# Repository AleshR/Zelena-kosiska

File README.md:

Zelena-kosiska
Pilot project of powerline communication modem

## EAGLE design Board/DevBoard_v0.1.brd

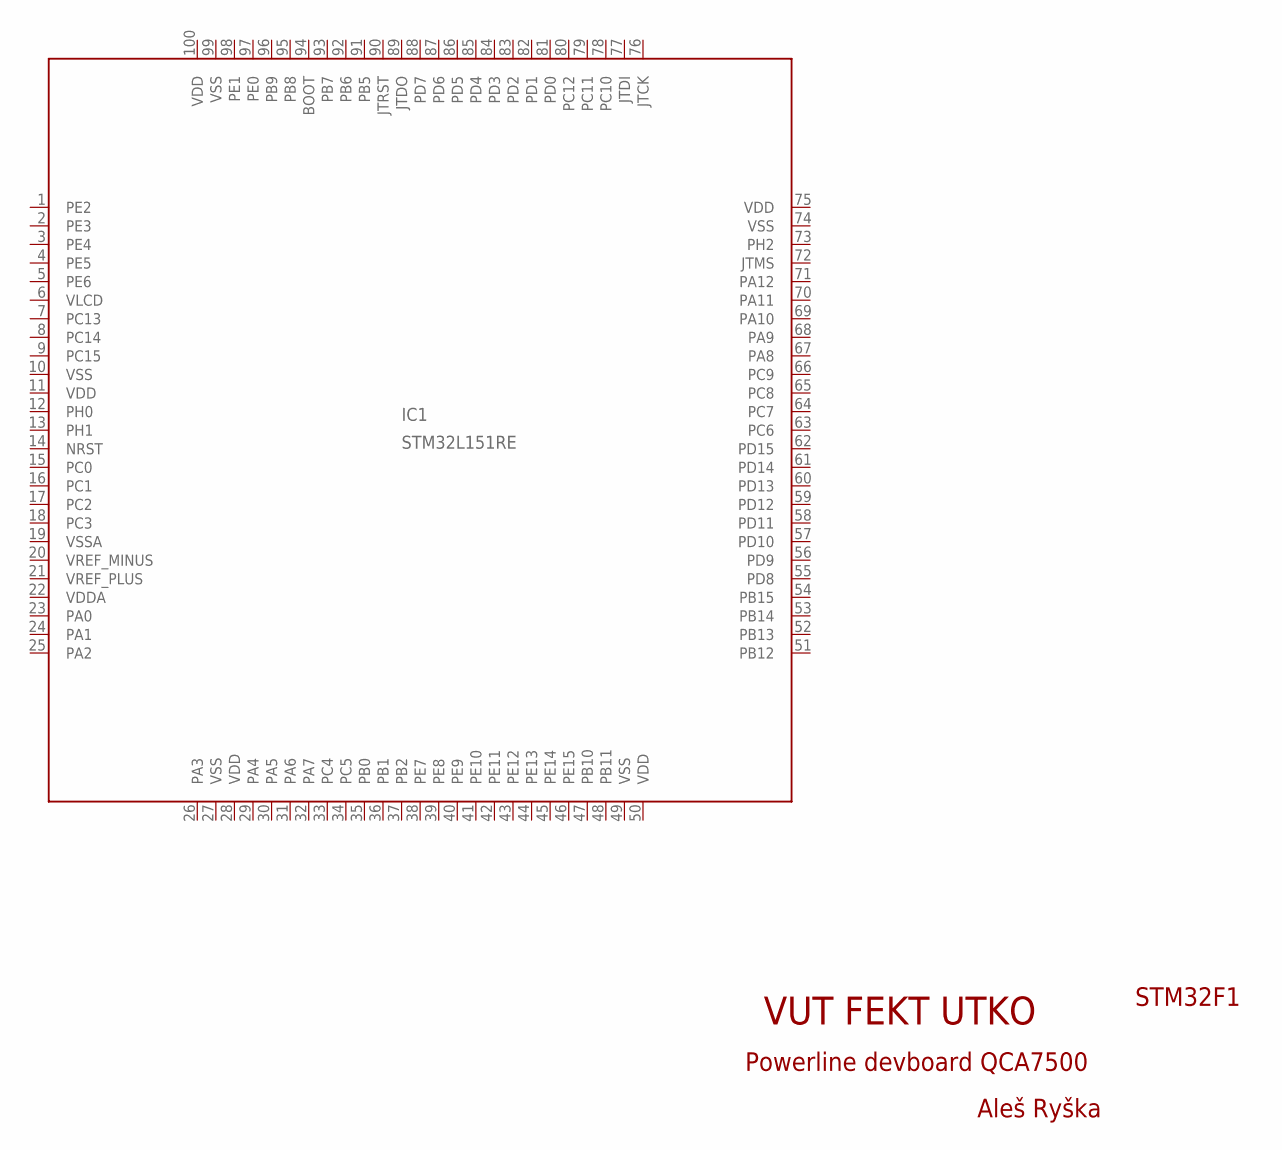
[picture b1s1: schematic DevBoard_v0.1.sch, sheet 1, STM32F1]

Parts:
IC1: STM32L151RE; LQFP100_14X14

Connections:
VDD: IC1.11 (VDD), IC1.28 (VDD), IC1.50 (VDD), IC1.75 (VDD), IC1.100 (VDD); also elsewhere on the board
VDDA: IC1.22 (VDDA)
VSS: IC1.10 (VSS), IC1.27 (VSS), IC1.49 (VSS), IC1.74 (VSS), IC1.99 (VSS); also elsewhere on the board
VSSA: IC1.19 (VSSA)

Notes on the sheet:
VUT FEKT UTKO
Powerline devboard QCA7500
STM32F1
Aleš Ryška

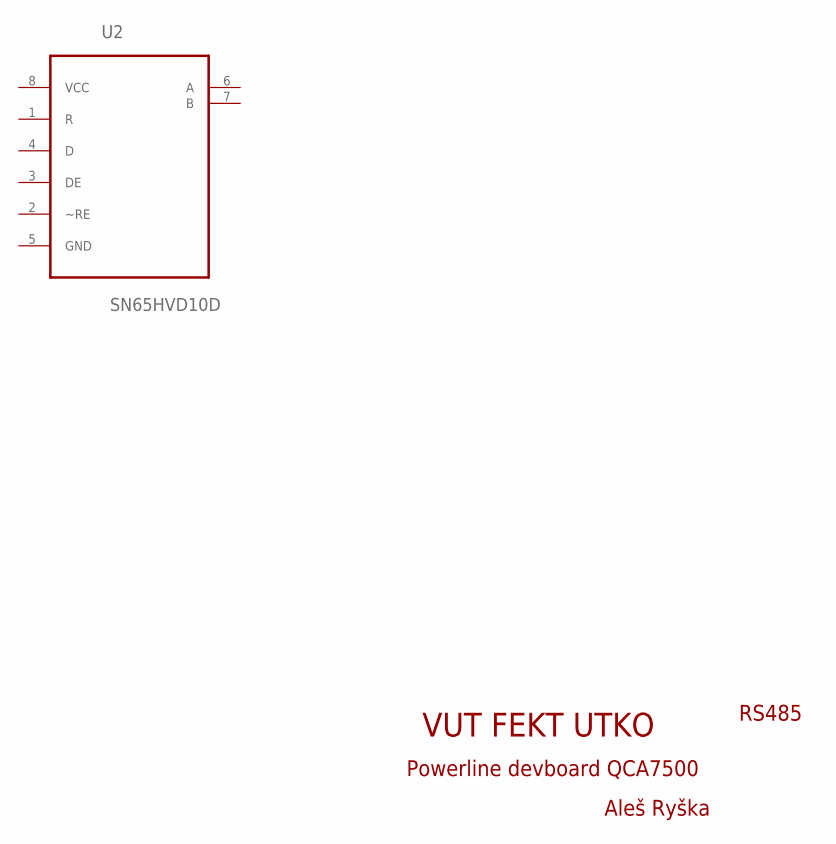
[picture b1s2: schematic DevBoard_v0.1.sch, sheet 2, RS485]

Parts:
U2: SN65HVD10D; SOIC127P600X175-8N

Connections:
VCC: U2.8 (VCC); also elsewhere on the board

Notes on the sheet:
VUT FEKT UTKO
Powerline devboard QCA7500
RS485
Aleš Ryška

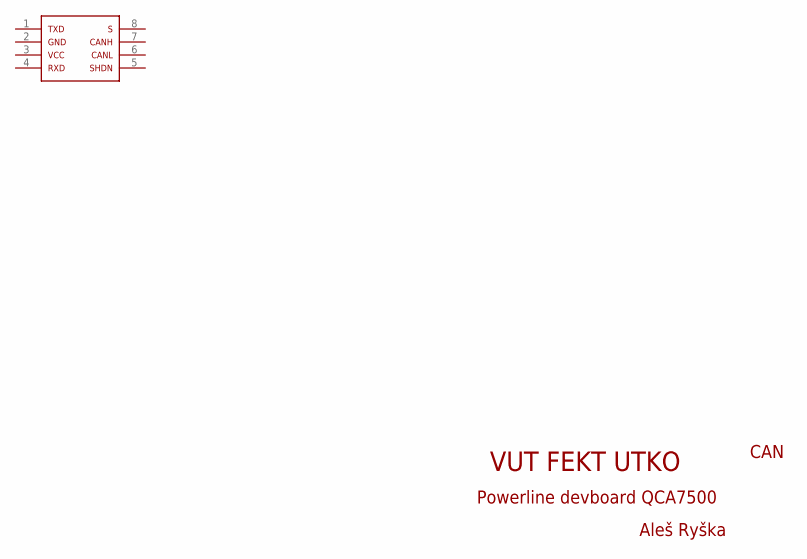
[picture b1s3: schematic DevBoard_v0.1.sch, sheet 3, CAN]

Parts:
U$2: TCAN330; SOP65P280X145-8N

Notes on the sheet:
VUT FEKT UTKO
Powerline devboard QCA7500
CAN
Aleš Ryška

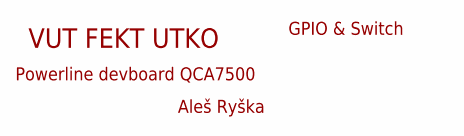
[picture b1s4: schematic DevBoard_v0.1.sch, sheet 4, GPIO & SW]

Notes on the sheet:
VUT FEKT UTKO
Powerline devboard QCA7500
GPIO & Switch
Aleš Ryška

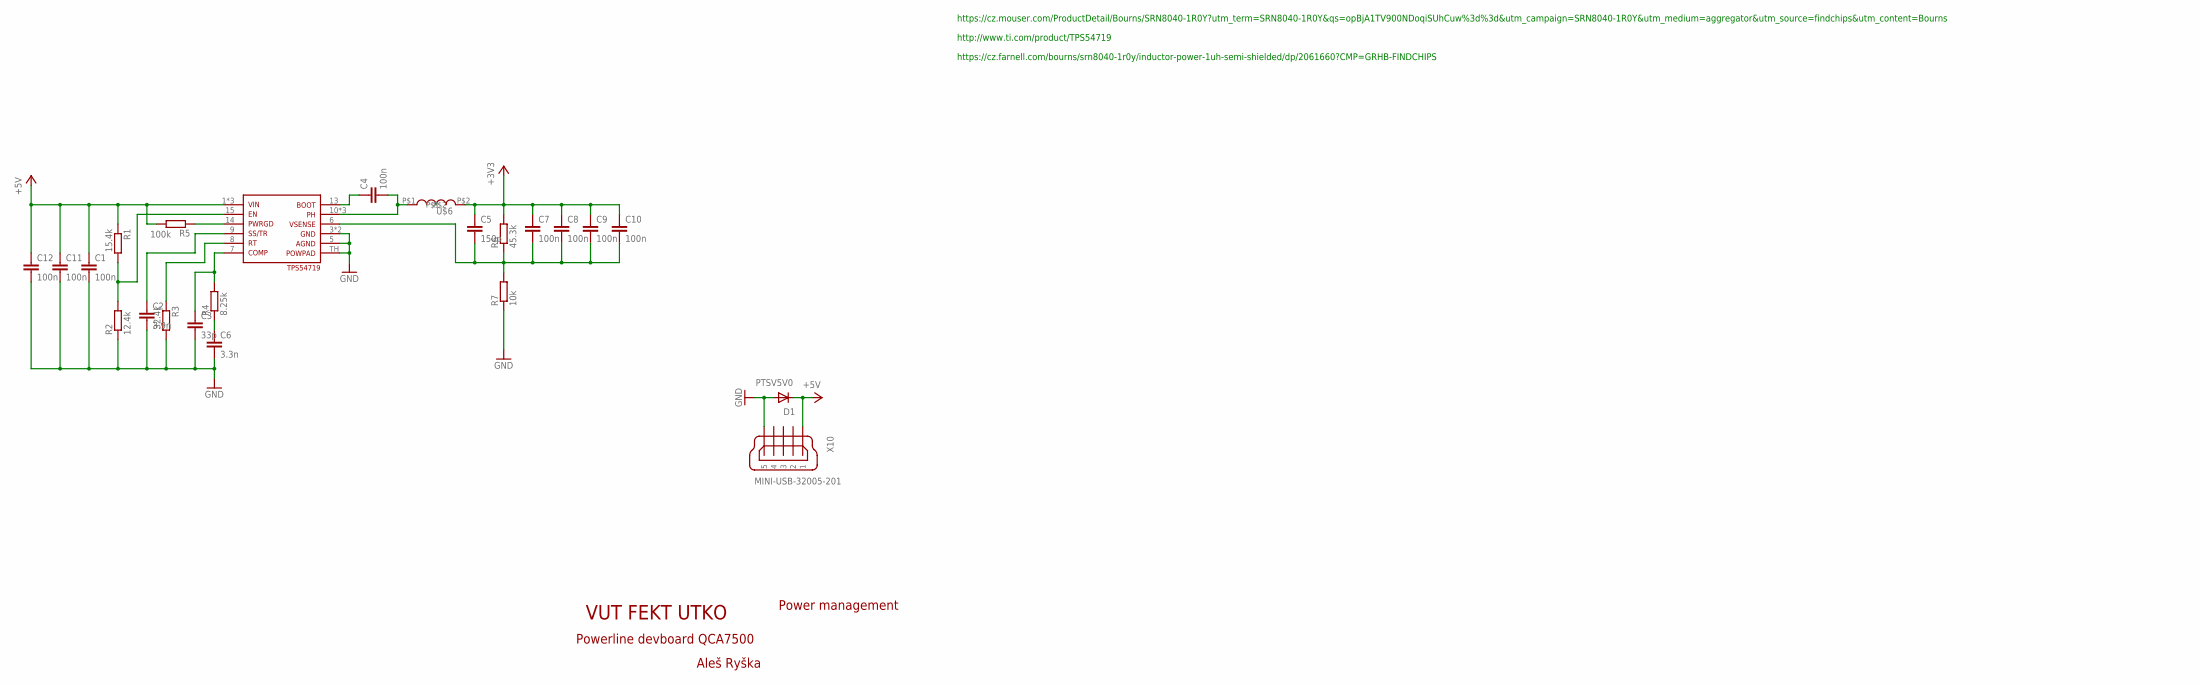
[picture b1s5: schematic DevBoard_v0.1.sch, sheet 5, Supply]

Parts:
C1, C4, C7, C8, C9, C10, C11, C12: 100n; C0805
C2: 3.9n; C0805
C3: 33p; C0805
C5: 150p; C0805
C6: 3.3n; C0805
D1: PTSV5V0; SOD123
R1: 15.4k; R0603
R2: 12.4k; R0603
R3: 32.4k; R0603
R4: 8.25k; R0603
R5: 100k; R0603
R6: 45.3k; R0603
R7: 10k; R0603
U$3: TPS54719; QFN16
U$6: 1u; SRN8040
X10: MINI-USB-32005-201; 32005-201

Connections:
+3V3: C5.1, C7.1, C8.1, C9.1, C10.1, R6.2, U$6.P$2; also elsewhere on the board
+5V: C1.1, C11.1, C12.1, D1.C, R1.1, R5.2, U$3.1 (V_IN), U$3.2 (V_IN), U$3.16 (V_IN), X10.1
GND: C1.2, C2.2, C3.2, C6.2, C11.2, C12.2, D1.A, R2.1, R3.2, R7.1, U$3.3 (GND), U$3.4 (GND), U$3.5 (AGND), U$3.TH (PPAD), X10.5; also elsewhere on the board
unnamed: R1.2, R2.2, U$3.15 (EN)
unnamed: C2.1, U$3.9 (SS/TR)
unnamed: R3.1, U$3.8 (RT)
unnamed: C3.1, R4.2, U$3.7 (COMP)
unnamed: R5.1, U$3.14 (PWRGD)
unnamed: C6.1, R4.1
unnamed: C4.1, U$3.13 (BOOT)
unnamed: C4.2, U$3.10 (PH), U$3.11 (PH), U$3.12 (PH), U$6.P$1
unnamed: C5.2, C7.2, C8.2, C9.2, C10.2, R6.1, R7.2, U$3.6 (VSNS)

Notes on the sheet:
VUT FEKT UTKO
Powerline devboard QCA7500
Power management
Aleš Ryška
http://www.ti.com/product/TPS54719
https://cz.mouser.com/ProductDetail/Bourns/SRN8040-1R0Y?utm_term=SRN8040-1R0Y&qs=opBjA1TV900NDoqiSUhCuw%3d%3d&utm_campaign=SRN8040-1R0Y&utm_medium=aggregator&utm_source=findchips&utm_content=Bourns
https://cz.farnell.com/bourns/srn8040-1r0y/inductor-power-1uh-semi-shielded/dp/2061660?CMP=GRHB-FINDCHIPS

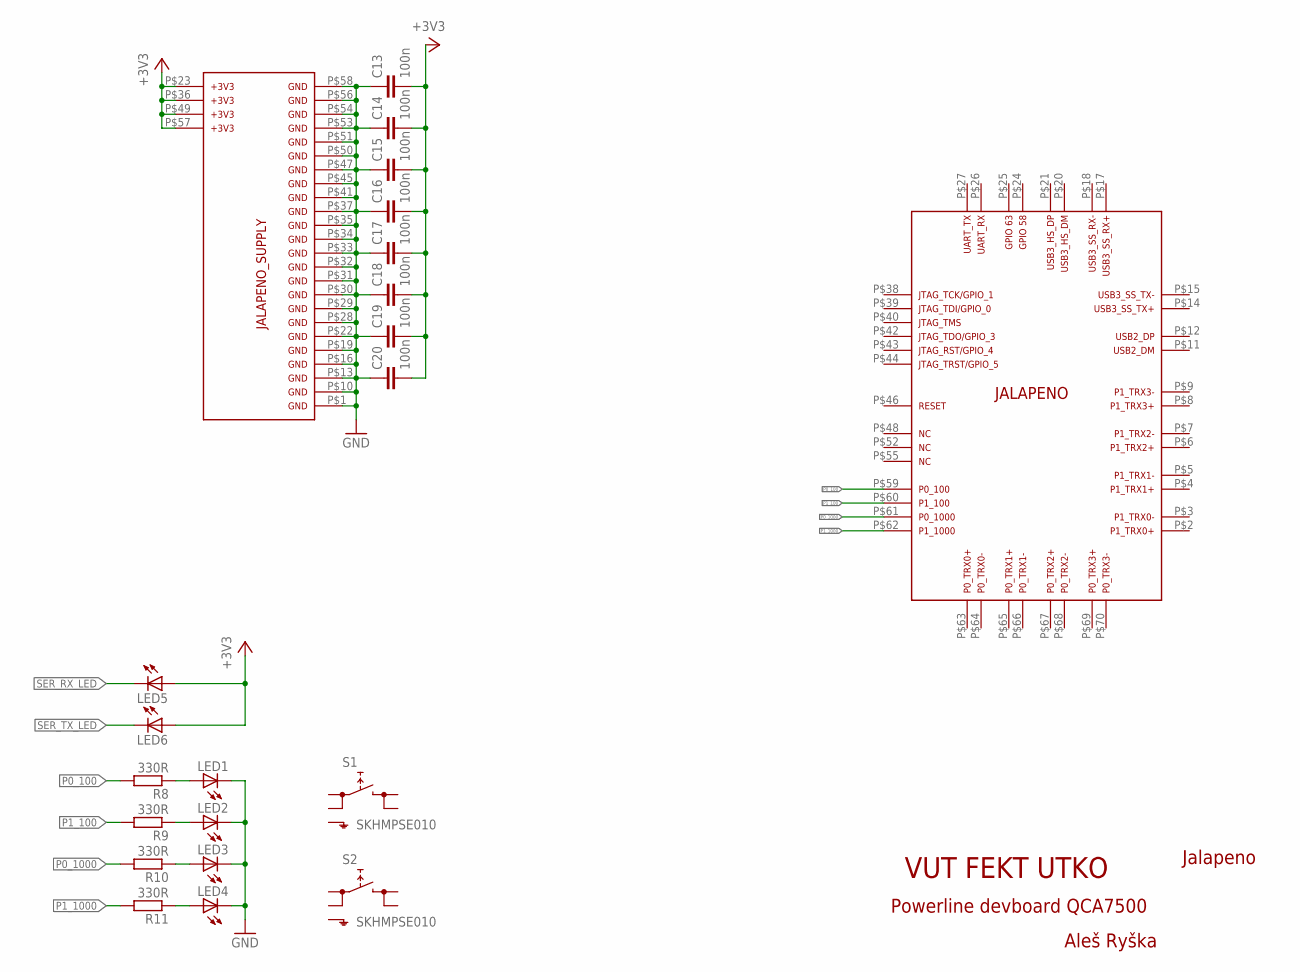
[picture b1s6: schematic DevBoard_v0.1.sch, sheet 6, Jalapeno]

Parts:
C13, C14, C15, C16, C17, C18, C19, C20: 100n; C0805
LED1, LED2, LED3, LED4, LED5, LED6: LED_E; LED_1206
R8, R9, R10, R11: 330R; R0603
S1, S2: SKHMPSE010; SKHMPXE010
U$1: JALAPENO

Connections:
+3V3: C13.2, C14.2, C15.2, C16.2, C17.2, C18.2, C19.2, C20.2, LED5.A, LED6.A, U$1.P$23, U$1.P$36, U$1.P$49, U$1.P$57; also elsewhere on the board
GND: C13.1, C14.1, C15.1, C16.1, C17.1, C18.1, C19.1, C20.1, LED1.C, LED2.C, LED3.C, LED4.C, U$1.P$1, U$1.P$10, U$1.P$13, U$1.P$16, U$1.P$19, U$1.P$22, U$1.P$28, U$1.P$29, U$1.P$30, U$1.P$31, U$1.P$32, U$1.P$33, U$1.P$34, U$1.P$35, U$1.P$37, U$1.P$41, U$1.P$45, U$1.P$47, U$1.P$50, U$1.P$51, U$1.P$53, U$1.P$54, U$1.P$56, U$1.P$58; also elsewhere on the board
unnamed: LED1.A, R8.1
unnamed: LED2.A, R9.1
unnamed: LED3.A, R10.1
unnamed: LED4.A, R11.1
P0_100: R8.2, U$1.P$59 (P0_100)
P0_1000: R10.2, U$1.P$61 (P0_1000)
P1_100: R9.2, U$1.P$60 (P1_100)
P1_1000: R11.2, U$1.P$62 (P1_1000)
SER_RX_LED: LED5.C
SER_TX_LED: LED6.C

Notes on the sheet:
VUT FEKT UTKO
Powerline devboard QCA7500
Jalapeno
Aleš Ryška

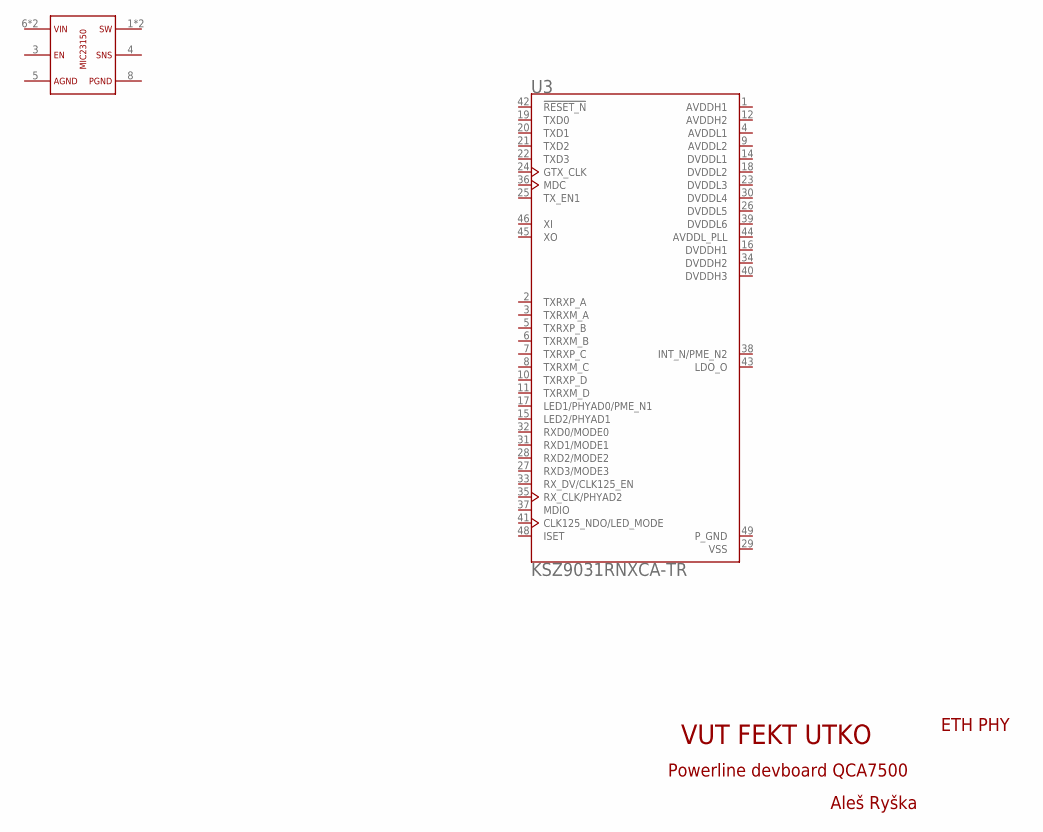
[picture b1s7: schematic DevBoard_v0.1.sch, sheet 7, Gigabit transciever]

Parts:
U3: KSZ9031RNXCA-TR; QFN50P700X700X90-49N
U$5: MIC23150; DFN8G-0.5-2X2MM

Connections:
AVDDH1: U3.1 (AVDDH1)
AVDDH2: U3.12 (AVDDH2)
AVDDL1: U3.4 (AVDDL1)
AVDDL2: U3.9 (AVDDL2)
AVDDL_PLL: U3.44 (AVDDL_PLL)
DVDDH1: U3.16 (DVDDH1)
DVDDH2: U3.34 (DVDDH2)
DVDDH3: U3.40 (DVDDH3)
DVDDL1: U3.14 (DVDDL1)
DVDDL2: U3.18 (DVDDL2)
DVDDL3: U3.23 (DVDDL3)
DVDDL4: U3.30 (DVDDL4)
DVDDL5: U3.26 (DVDDL5)
DVDDL6: U3.39 (DVDDL6)
P_GND: U3.49 (P_GND)
VSS: U3.29 (VSS); also elsewhere on the board

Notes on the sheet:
VUT FEKT UTKO
Powerline devboard QCA7500
ETH PHY
Aleš Ryška

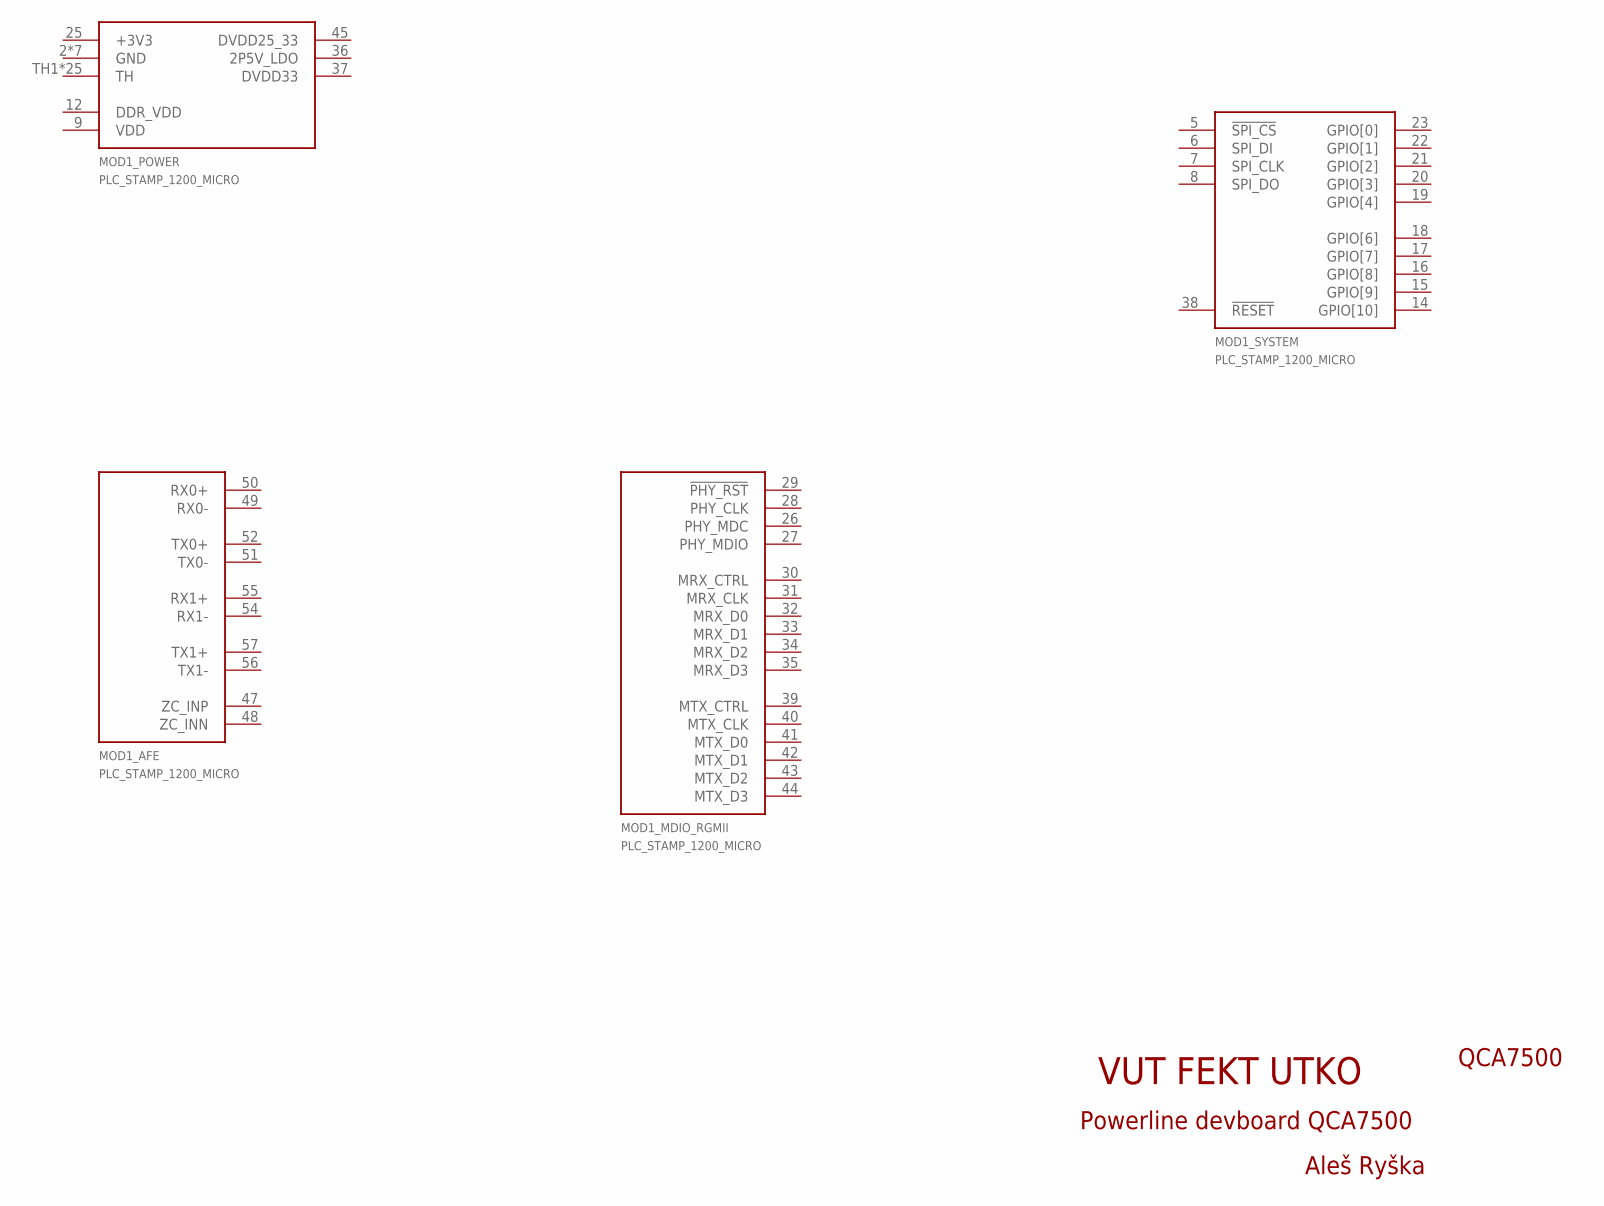
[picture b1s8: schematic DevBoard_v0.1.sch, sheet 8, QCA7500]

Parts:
MOD1: PLC_STAMP_1200_MICRO

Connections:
+3V3: MOD1.25 (+3V3); also elsewhere on the board
DDR_VDD: MOD1.12 (DDR_VDD)
DVDD25_33: MOD1.45 (DVDD25_33)
GND: MOD1.2 (GND), MOD1.3 (GND), MOD1.4 (GND), MOD1.10 (GND), MOD1.11 (GND), MOD1.13 (GND), MOD1.24 (GND); also elsewhere on the board
TH: MOD1.TH1 (TH), MOD1.TH2 (TH), MOD1.TH3 (TH), MOD1.TH4 (TH), MOD1.TH5 (TH), MOD1.TH6 (TH), MOD1.TH7 (TH), MOD1.TH8 (TH), MOD1.TH9 (TH), MOD1.TH10 (TH), MOD1.TH11 (TH), MOD1.TH12 (TH), MOD1.TH13 (TH), MOD1.TH14 (TH), MOD1.TH15 (TH), MOD1.TH16 (TH), MOD1.TH17 (TH), MOD1.TH18 (TH), MOD1.TH19 (TH), MOD1.TH20 (TH), MOD1.TH21 (TH), MOD1.TH22 (TH), MOD1.TH23 (TH), MOD1.TH24 (TH), MOD1.TH25 (TH)
VDD: MOD1.9 (VDD); also elsewhere on the board

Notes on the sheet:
VUT FEKT UTKO
Powerline devboard QCA7500
QCA7500
Aleš Ryška

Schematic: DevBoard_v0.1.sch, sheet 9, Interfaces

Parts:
X1, X2: USB-787616; USB
X3: MINI-USB_SHIELD4P-85-32006-001-1; 85-32006-001-1
X4, X5: JP006821U; JP

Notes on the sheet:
VUT FEKT UTKO
Powerline devboard QCA7500
PHY connectors
Aleš Ryška

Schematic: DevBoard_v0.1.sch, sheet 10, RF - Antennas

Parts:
X6, X7: LTI-SASF54GT
X8, X9: SMA-SMD

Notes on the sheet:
VUT FEKT UTKO
Powerline devboard QCA7500
RF - Antennas
Aleš Ryška

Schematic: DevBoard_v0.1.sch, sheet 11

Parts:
D2: PTSV5V0; SOD123
IC2: FT230XS; SSOP16
X11: MINI-USB-32005-201; 32005-201

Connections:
GND: D2.A, IC2.5 (GND), IC2.13 (GND), X11.5; also elsewhere on the board
unnamed: D2.C, X11.1
VCC: IC2.12 (VCC); also elsewhere on the board
VCCIO: IC2.3 (VCCIO)

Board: 2 copper layers, 62 parts (0 on the bottom side), 25 nets, no tracks yet.

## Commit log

2018-09-25 Uploaded pilot project
    All files
2018-09-25 Created dict. "Jalapeno"
    Jalapeno schematic and datasheet in separate folder
2018-09-25 Upload files from Gdrive
    uploaded all files from old project (Gdrive)
2018-09-25 Uploaded libraries
2018-09-25 Moved filed to Dokumenty
    Martin_Strbacka.pdf
    ukoly-ryska.pdf
2018-09-26 Deleted some files
